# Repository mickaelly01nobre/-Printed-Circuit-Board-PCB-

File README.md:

## STEVAL-ISV012V1 

The STEVAL-ISV012V1 demonstration board is based on the SPV1040 solar voltage boost converter and the L6924D single cell Li-ion battery charger 
The SPV1040 device is a high efficiency, low power, low voltage, monolithic step-up converter with an input voltage range from 0.3 V to 5.5 V, 
and is capable of maximizing the energy generated by even a single solar cell (or fuel cell), where low input voltage handling capability is 
extremely important.

Thanks to the embedded MPPT algorithm, even under varying environmental conditions (such as irradiation, dirt, temperature) the SPV1040 offers 
maximum efficiency in terms of power harvested from the cells and transferred to the output.

The SPV1040 protects itself and other application devices by stopping the PWM switching if either the maximum current threshold (up to 2 A) is 
reached or the maximum temperature limit (up to 155 °C) is exceeded.

The L6924D device is a fully monolithic battery charger dedicated to single cell Lithium-ion/Lithium-ion polymer battery packs. It is the ideal 
solution for space-limited applications such as PDAs, handheld equipment, cellular phones, and digital cameras.

The L6924D normally works as a linear charger when powered from an external voltage regulated adapter. The device can also work in “quasi-pulse” 
charger mode when powered from a current limited adapter like that of a solar panel. To work in this condition, the charging current of the device 
should be set to a level higher than the solar panel maximum peak current.

Thanks to the L6924D’s very low minimum input voltage (down to 2.5 V), during the fast-charge phase the output voltage of the solar panel drops down 
to the battery voltage plus the voltage drop across the power MOSFET of the charger.

The main advantage of the quasi-pulse charging mode is that it shares the simplicity of the linear approach, where the power dissipated is dramatically 
reduced, thereby maximizing the charge rate from the solar panel.

The Li-ion battery solar charger with embedded (MPPT) and quasi-pulse charging mode is “best-in-class” in terms of system efficiency, allowing battery 
charging while maximizing available solar panel power.

In the STEVAL-ISV012V1 demonstration board, the L6924D is supplied by the output stage of the SPV1040, which is supplied by a 400 mW PV panel.

### Technical Features

SPV1040: solar boost converter with embedded maximum power point tracking (MPPT)
* Proprietary “perturb & observe” MPPT algorithm
* Up to 95% efficiency
* Very low input voltage (down to 0.3 V)
* Input reverse polarity protection
* Thermal shut-down
* Overcurrent protection
* Enable pin
  
L6924D: Fully integrated linear charger solution with power MOSFET, reverse blocking diode and battery thermal control

* 1% battery voltage regulation accuracy
* Up to 1 A charge current with 7% accuracy
* Closed loop thermal regulation protection for output current control
* Low battery leakage current
* Embedded quasi-pulse charging mode maximizes charge rate from solar panel
* Selectable 4.1 V and 4.2 V output voltage
* JEITA compliant with external circuit
* Programmable charge, fast charge (up to 1 A), pre-charge, termination current, pre-charge mode voltage threshold, charge timer
* Multifunction pin for flexible charge process termination
* Status outputs to drive LEDs or host processor interface
* Battery absence detection
* NTC or PTC thermistor interface for battery temperature monitoring and protection
* RoHS compliant

<div align="center">

</div>

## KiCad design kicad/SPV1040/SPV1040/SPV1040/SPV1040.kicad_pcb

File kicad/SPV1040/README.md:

#  SPV1040

The SPV1040 device is a low power, low voltage, monolithic step-up converter with an input voltage range from 0.3 V to 5.5 V, capable of maximizing the energy generated by solar cells (or fuel cells), where low input voltage handling capability is extremely important. Thanks to the embedded MPPT algorithm, even under varying environmental conditions (such as irradiation, dirt, temperature) the SPV1040 offers maximum efficiency in terms of power harvested from the cells and transferred to the output. The device employs a voltage regulation loop, which fixes the charging battery voltage via a resistor divider.

It is possible to set the maximum output current according to charging requirements by a sense resistor .

The SPV1040 protects itself and other application devices by stopping the PWM switching if either the maximum current threshold (up to 1.8 Apk) is reached or the maximum temperature limit (up to 155 °C) is exceeded. An additional built-in feature of the SPV1040 is the input source reverse polarity protection, which prevents damage in case of reverse connection of the solar panel on the input.

### Technical Features

* 0.3 V to 5.5 V operating input voltage
* 140 mΩ internal synchronous rectifier
* 120 mΩ internal power active switch
* 100 kHz fixed PWM frequency
* Duty cycle controlled by MPPT algorithm
* Output voltage regulation, overcurrent and overtemperature protection
* Input source reverse polarity protection
* Built-in soft-start
* Up to 95% efficiency
* TSSOP8 package 3x4.4 mm

  <div align="center">

</div>

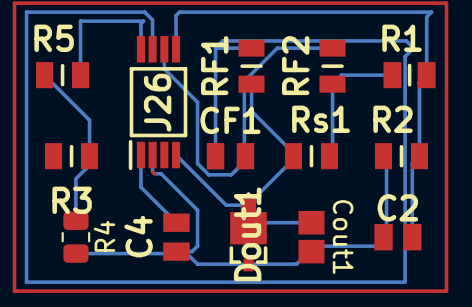
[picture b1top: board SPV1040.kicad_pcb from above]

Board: 2 copper layers, 14 parts (0 on the bottom side), 8 nets.

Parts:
C2, C4: C0805C102K5RAC; CAPC2012X88N
CF1: GRM21BR71C105KA01L; CAPC2012X145N
Cout1: Cout1; CAPC220145_140N_KEM
Dout1: SMM4F5.0A-TR; SMM4F15ATR
J26: SPV1040T; SOP65P640X120-8N
R1: MCHV05WAJ0225T5E; RESC2013X65N
R2: CRCW0805820KFKEA; RESC2012X50N
R3: CRCW08051K00FKEA; RESC2012X50N
R4: DNM; R_0805_2012Metric
R5: CRCW08050000Z0EA; RESC2012X50N
RF1, RF2: CRCW08051K00FKEA; RESC2012X50N
Rs1: CRCW08050000Z0EA; RESC2012X50N

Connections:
unnamed: C2.1, C4.2, Cout1.2, Dout1.2 (A), J26.2 (GND), R2.2, R4.2
unnamed: Cout1.1, Dout1.1 (K_1), Dout1.3 (K_2), J26.4 (VOUT), RF1.2, Rs1.1
unnamed: CF1.2, J26.6 (ICTRL_MINUS), RF2.1
unnamed: CF1.1, J26.7 (ICTRL_PLUS), RF1.1
unnamed: C4.1, J26.1 (MPP-SET), R3.1, R4.1, R5.1
unnamed: C2.2, J26.5 (VCTRL), R1.2, R2.1
unnamed: J26.8 (XSHUT), R5.2
unnamed: R1.1, RF2.2, Rs1.2

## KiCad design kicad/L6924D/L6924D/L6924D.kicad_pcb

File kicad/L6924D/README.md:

# L6924D 

The L6924D is a fully monolithic battery charger dedicated to single-cell Li-Ion/Polymer battery packs. It is the ideal solution for space-limited applications, like handheld equipment, and digital cameras. It integrates all of the power elements (the power MOSFET, reverse blocking diode and the sense resistor) in a small VFQFPN16 (3 x 3 mm) package. When an external voltage-regulated wall adapter is used, the L6924D works in linear mode, and charges the battery in a constant current/constant voltage (CC/CV) profile. Moreover, when a current-limited adapter is used, the device can operate in quasi-pulse mode, dramatically reducing the power dissipation. Regardless of the charging approach, a closed-loop thermal control avoids device overheating. The device has an operating input voltage ranging from 2.5 V to 12 V. The L6924D allows the user to program many parameters, such as pre-charge current, fast-charge current, pre-charge voltage threshold, end-of-charge current threshold, and charge timer. The L6924D offers two open collector outputs for diagnostic purposes, which can be used to either drive two external LEDs or communicate with a host microcontroller. Finally, the L6924D also provides very flexible control of the charge process termination and gas gauge capability, as well as other functions, such as checking for battery presence, and monitoring and protecting the battery from unsafe thermal conditions.

### Technical Features

* Fully integrated solution, with a power MOSFET, reverse blocking diode, sense resistor, and thermal protection
* Ideal for coke and graphite anode single-cell LI-ION packs
* Both linear and quasi-pulse operation
* Closed loop thermal control
* USB BUS-compatible
* Programmable charge current up to 1 A
* Programmable pre-charge current
* Programmable end-of-charge current
* Programmable pre-charge voltage threshold
* Programmable charge timer
* Programmable output voltage at 4.1 V and 4.2 V, with ± 1 % output voltage accuracy
* (NTC) or (PTC) thermistor interface for battery temperature monitoring and protection
* Flexible charge process termination
* Status outputs to drive LEDs or to interface with a host processor
* Small VFQFPN 16-lead package (3 x 3 mm)

<div align="center">

</div>

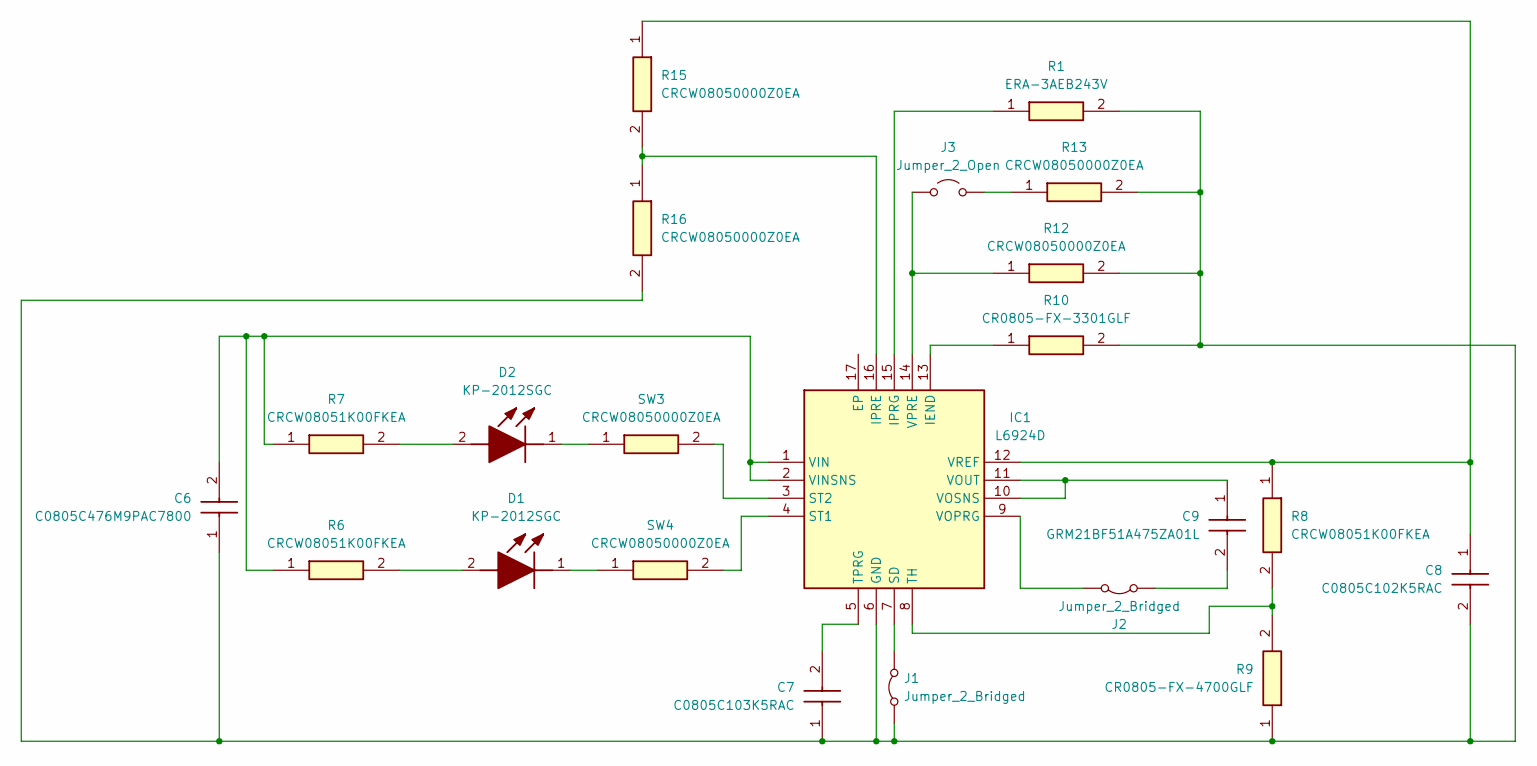
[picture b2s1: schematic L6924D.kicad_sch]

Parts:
C6: C0805C476M9PAC7800; CAPC2012X145N; Mouser Part Number 80-C0805C476M9P7800
C7: C0805C103K5RAC; CAPC2012X88N; Mouser Part Number 80-C0805C103K5RAC
C8: C0805C102K5RAC; CAPC2012X88N; Mouser Part Number 80-C0805C102K5RAC
C9: GRM21BF51A475ZA01L; CAPC2012X145N; Mouser Part Number 81-GRM40Y5V475Z010AL
D1, D2: KP-2012SGC; LEDC2012X110N; Manufacturer_Part_Number KP-2012SGC
IC1: L6924D; QFN50P300X300X100-17N-D; Manufacturer_Part_Number L6924D; Mouser Part Number 511-L6924D
J1, J2: Jumper_2_Bridged; SolderJumper-2_P1.3mm_Bridged2Bar_Pad1.0x1.5mm
J3: Jumper_2_Open; SolderJumper-2_P1.3mm_Open_Pad1.0x1.5mm
R1: ERA-3AEB243V; ERA3AEB101V; Mouser Part Number 667-ERA-3AEB243V
R6, R7, R8: CRCW08051K00FKEA; RESC2012X50N; Mouser Part Number 71-CRCW0805-1.0K-E3
R9: CR0805-FX-4700GLF; RESC2012X60N; Mouser Part Number 652-CR0805-FX4700GLF
R10: CR0805-FX-3301GLF; RESC2012X60N; Mouser Part Number 652-CR0805-FX3301GLF
R12, R13, R15, R16: CRCW08050000Z0EA; RESC2012X50N; Mouser Part Number 71-CRCW0805-0-E3
SW3, SW4: CRCW08050000Z0EA; RESC2012X50N; Mouser Part Number 71-CRCW0805-0-E3

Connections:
unnamed: D1.2 (A), R6.2
unnamed: D1.1 (K), SW4.1
unnamed: D2.2 (A), R7.2
unnamed: D2.1 (K), SW3.1
unnamed 4: C6.1, C7.1, C8.2, IC1.6 (GND), J1.1 (A), R1.2, R9.1, R10.2, R12.2, R13.2, R16.2; also elsewhere on the board
unnamed: IC1.13 (IEND), R10.1
unnamed: IC1.16 (IPRE), R15.2, R16.1
unnamed 7: IC1.15 (IPRG), R1.1; also elsewhere on the board
unnamed: IC1.7 (SD), J1.2 (B)
unnamed: IC1.4 (ST1), SW4.2
unnamed: IC1.3 (ST2), SW3.2
unnamed: IC1.8 (TH), R8.2, R9.2
unnamed: C7.2, IC1.5 (TPRG)
unnamed: C6.2, IC1.1 (VIN), IC1.2 (VINSNS), R6.1, R7.1
unnamed: IC1.9 (VOPRG), J2.1 (A)
unnamed: C9.1, IC1.10 (VOSNS), IC1.11 (VOUT)
unnamed: IC1.14 (VPRE), J3.1 (A), R12.1
unnamed: C8.1, IC1.12 (VREF), R8.1, R15.1
unnamed: C9.2, J2.2 (B)
unnamed: J3.2 (B), R13.1

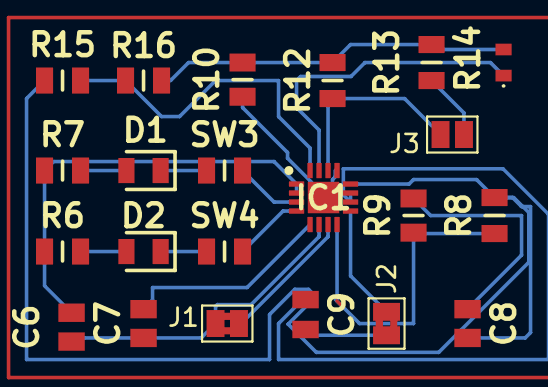
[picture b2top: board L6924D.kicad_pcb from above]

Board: 2 copper layers, 22 parts (0 on the bottom side), 20 nets.

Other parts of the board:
R14: ERA-3AEB243V; ERA3AEB101V

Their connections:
unnamed 4: R14.2; also elsewhere on the board
unnamed 7: R14.1; also elsewhere on the board

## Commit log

2024-07-22 Charger Module
2024-07-22 Create ccc
2024-07-22 Create cc
2024-08-05 Changed
